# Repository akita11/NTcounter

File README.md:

# NTcounter

赤外線の送信機・受信機のペアで、その間を横切った数をカウントするシステムです。NT金沢のような開放空間での来場者カウントに使います。横切りがあった時刻と積算カウント数をmicroSDカードに記録していきます。

# 用意するもの
## 送信機
- [ATtiny10](http://akizukidenshi.com/catalog/g/gI-04575/)
- [nMOS](http://akizukidenshi.com/catalog/g/gI-06051/)
- [赤外線LED](http://akizukidenshi.com/catalog/g/gI-12612/)
- USB Type-Cコネクタ (a)http://www.aitendo.com/product/17279 または (b)http://akizukidenshi.com/catalog/g/gC-14356/
- チップ抵抗 5.1kΩ(1608)×2個、1kΩ(1608)×1個
- チップLED 緑(1608)×1個
- プリント基板 NTcounterTX
- [100均ルーペNo.13058]（セリア等で売っているようです）

- 厚紙
- MDF板(厚さ6mm) ※アクリル板(厚さ5mm)でもOK
- USBモバイルバッテリ等の電源と、それをつなぐUSB Type-C等のケーブル
- M3x12ネジ+M3ナット×2組

## 受信機
- [M5Stack Basic](https://www.switch-science.com/catalog/3647/)
- [M5Stackバッテリモジュール](https://www.switch-science.com/catalog/3653/)
- [M5Stackコネクタ](https://www.switch-science.com/catalog/3654/)
- [赤外線リモコン受信機](http://akizukidenshi.com/catalog/g/gI-04659/)
- [スライドスイッチ](http://akizukidenshi.com/catalog/g/gP-08789/)
- [ピンソケット1x3p](http://akizukidenshi.com/catalog/g/gC-10098/)
- プリント基板 NTcounterRX
- microSDカード
- アクリル板(厚さ5mm)

※おまけ：プリント基板NTcounerRXは、M5StackのGroveコネクタのポートA, B, C, D, Eの拡張にも使えます

# 作り方

## 送信機

1. プリント基板NTcounterTXに部品をとりつけます。USB Type-Cコネクタとして(a)を用いる場合はCN4に、(b)を使う場合はCN2にとりつけます。なおCN4につける(a)の方がはんだ付けはしやすいです。
2. 、ファームウエアNTcounterTX.hexを書き込みます。(NTcounterTX.inoをArduinoIDEからコンパイルして書き込んでもOK。（参考: [ArduinoIDEでATtiny10を開発・書き込み ](https://make.kosakalab.com/make/electronic-work/arduino-ide/arduino_tpi/)
3. MDF板(厚さ6mm)にNTcounerTX_lens.svgの右側の部品をレーザーカッター等でカットし、1.を固定します。

4. 厚紙にNTcounerTX_lens.svgの左側の部品をレーザーカッター等でカットします。このとき、用いるUSB-Cコネクタが(a)の場合と(b)の場合で少し加工データが異なるので、NTcounerTX_lens.svgを適宜修正してください。

5. 100均ルーペの3倍を、取っ手を外して、1.とともに、2.で囲って固定します。

## 受信機

1. プリント基板NTcounterRXに部品をとりつけます。（※M5Stackコネクタのオス・メスを取り付ける面を間違えないように注意。M5Stack本体(M5Core)に差し込んだ状態でシルク文字が外から見える向き）
2. VSCodeでNTcounerRX内のファームウエアの以下の箇所を自分の環境に合わせて修正します。
  - #define DEV_NAME "NTcounter" ← デバイス名。ログファイルの冒頭に記録される
  - const char* ssid       = "****"; ← 起動時に接続するWiFiアクセスポイントのSSID
  - const char* password   = "****"; ← 同パスワード
3. ファームウエアをビルドして書き込みます。
4. アクリル板(厚さ5mm)をNTcounterRX_spaccer.svgのようにレーザーカッター等でカットします。
5. M5StackのCore、1.とスペーサ、M5Stackバッテリユニット、、M5Stack底板を順にとりつけます。

# 使い方
1. USBモバイルバッテリ等からUSB TypeｰCケーブルで送信機に給電します。電源ランプが点灯します。
2. 受信機を充電後、microSDカードをとりつけて電源スイッチをONにします。なお受信機の起動時のみ、時刻あわせのためWiFi接続が必要です。起動後はWiFiは不要です。
3. 送信機と受信機を向かい合わせに、通路をはさむ両側に置ます。このとき、送信機の赤外光が受信機に届いていれば、受信機のディスプレイに表示される円が緑になります。円が赤い場合は、赤外光が届いていないので、向きを調整します。両者の間隔は1〜6mくらいまでは大丈夫なはずです。
4. この状態で、両者の間に障害物を置くと、受信機に表示される円が赤になり、その時点の時刻と積算カウント数が記録されます。
5. 動作がOKそうなら、受信機のM5StackのBボタン（中央ボタン）を押し、画面表示をOFFにすると、バッテリが長持ちします。（満充電で丸2日くらいはもつはず）

# Author

@akita11 (akita@ifdl.jp)

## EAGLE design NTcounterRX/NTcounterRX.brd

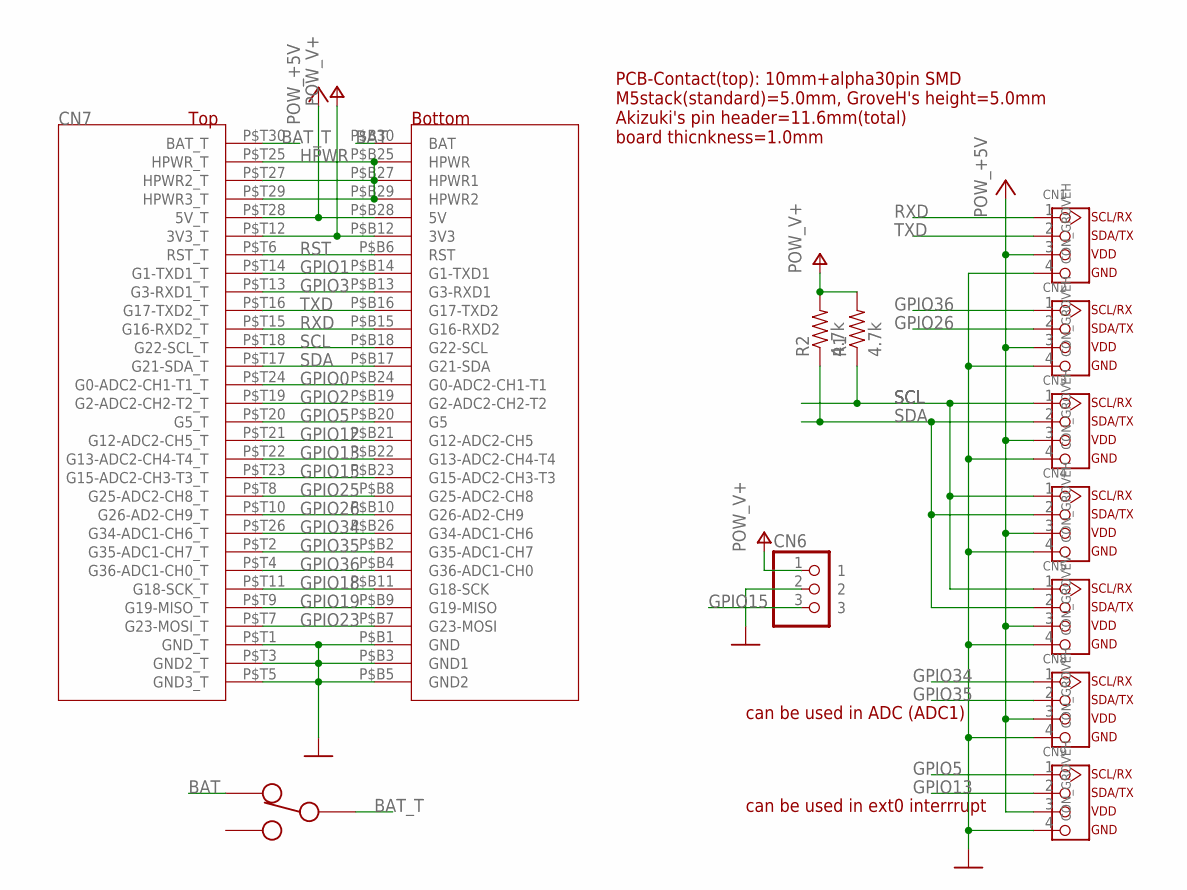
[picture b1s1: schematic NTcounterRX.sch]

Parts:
CN1, CN2, CN3, CN4, CN8, CN9: CON_GROVEH; CON_GROVE_H
CN5: CON_GROVEV; CON_GROVE_V
CN6: CON_PINHD-1X3R; 1X03R
CN7: MBUS_SEPBAT; MBUS_SEP_BAT_SHORT
R1, R2: 4.7k; 0603
SW1: SW_SLIDESK12D01; SW_SK12D01

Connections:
+5V: CN1.3, CN2.3, CN3.3, CN4.3, CN5.3, CN7.P$B28 (5V), CN7.P$T28 (5V_T), CN8.3, CN9.3
BAT: CN7.P$B30 (BAT), SW1.P$1
BAT_T: CN7.P$T30 (BAT_T), SW1.P$2
GND: CN1.4, CN2.4, CN3.4, CN4.4, CN5.4, CN6.2, CN7.P$B1 (GND), CN7.P$B3 (GND1), CN7.P$B5 (GND2), CN7.P$T1 (GND_T), CN7.P$T3 (GND2_T), CN7.P$T5 (GND3_T), CN8.4, CN9.4
GPIO0: CN7.P$B24 (G0-ADC2-CH1-T1), CN7.P$T24 (G0-ADC2-CH1-T1_T)
GPIO1: CN7.P$B14 (G1-TXD1), CN7.P$T14 (G1-TXD1_T)
GPIO2: CN7.P$B19 (G2-ADC2-CH2-T2), CN7.P$T19 (G2-ADC2-CH2-T2_T)
GPIO3: CN7.P$B13 (G3-RXD1), CN7.P$T13 (G3-RXD1_T)
GPIO5: CN7.P$B20 (G5), CN7.P$T20 (G5_T), CN9.1
GPIO12: CN7.P$B21 (G12-ADC2-CH5), CN7.P$T21 (G12-ADC2-CH5_T)
GPIO13: CN7.P$B22 (G13-ADC2-CH4-T4), CN7.P$T22 (G13-ADC2-CH4-T4_T), CN9.2
GPIO15: CN6.3, CN7.P$B23 (G15-ADC2-CH3-T3), CN7.P$T23 (G15-ADC2-CH3-T3_T)
GPIO18: CN7.P$B11 (G18-SCK), CN7.P$T11 (G18-SCK_T)
GPIO19: CN7.P$B9 (G19-MISO), CN7.P$T9 (G19-MISO_T)
GPIO23: CN7.P$B7 (G23-MOSI), CN7.P$T7 (G23-MOSI_T)
GPIO25: CN7.P$B8 (G25-ADC2-CH8), CN7.P$T8 (G25-ADC2-CH8_T)
GPIO26: CN2.2, CN7.P$B10 (G26-AD2-CH9), CN7.P$T10 (G26-AD2-CH9_T)
GPIO34: CN7.P$B26 (G34-ADC1-CH6), CN7.P$T26 (G34-ADC1-CH6_T), CN8.1
GPIO35: CN7.P$B2 (G35-ADC1-CH7), CN7.P$T2 (G35-ADC1-CH7_T), CN8.2
GPIO36: CN2.1, CN7.P$B4 (G36-ADC1-CH0), CN7.P$T4 (G36-ADC1-CH0_T)
HPWR: CN7.P$B25 (HPWR), CN7.P$B27 (HPWR1), CN7.P$B29 (HPWR2), CN7.P$T25 (HPWR_T), CN7.P$T27 (HPWR2_T), CN7.P$T29 (HPWR3_T)
P$3: SW1.P$3
RST: CN7.P$B6 (RST), CN7.P$T6 (RST_T)
RXD: CN1.1, CN7.P$B15 (G16-RXD2), CN7.P$T15 (G16-RXD2_T)
SCL: CN3.1, CN4.1, CN5.1, CN7.P$B18 (G22-SCL), CN7.P$T18 (G22-SCL_T), R1.1
SDA: CN3.2, CN4.2, CN5.2, CN7.P$B17 (G21-SDA), CN7.P$T17 (G21-SDA_T), R2.1
TXD: CN1.2, CN7.P$B16 (G17-TXD2), CN7.P$T16 (G17-TXD2_T)
V+: CN6.1, CN7.P$B12 (3V3), CN7.P$T12 (3V3_T), R1.2, R2.2

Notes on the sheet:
PCB-Contact(top): 10mm+alpha30pin SMD M5stack(standard)=5.0mm, GroveH's height=5.0mm Akizuki's pin header=11.6mm(total) board thicnkness=1.0mm
can be used in ext0 interrrupt
can be used in ADC (ADC1)

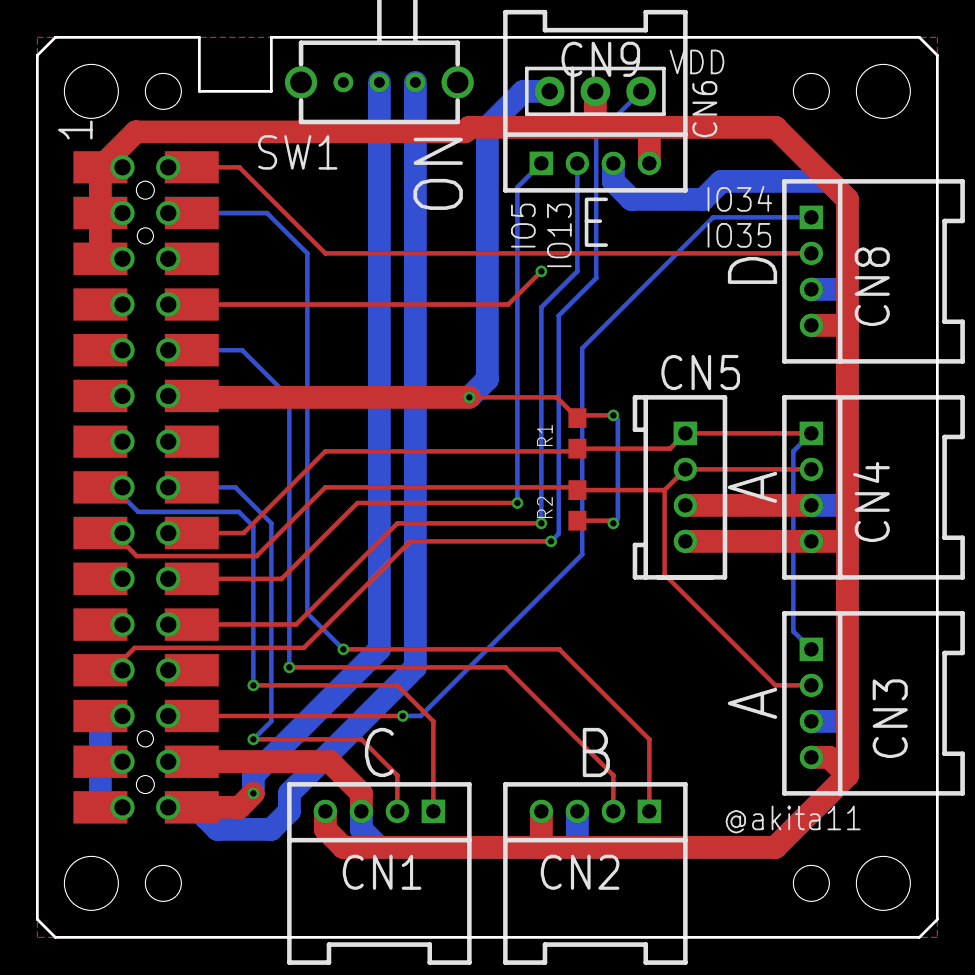
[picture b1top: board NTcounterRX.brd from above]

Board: 2 copper layers, 50.0 x 50.0 mm, 12 parts (0 on the bottom side), 27 nets.

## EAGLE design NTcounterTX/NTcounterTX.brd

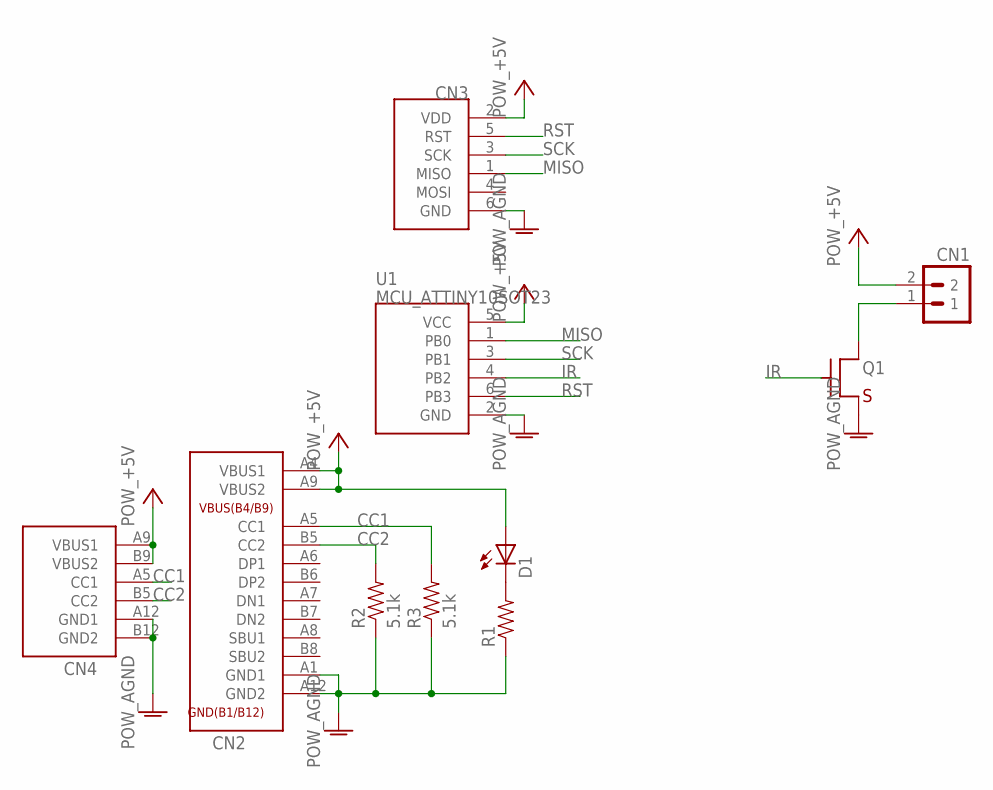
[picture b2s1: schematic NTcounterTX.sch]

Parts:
CN1: CON_PINHD-1X2LOCK; SPARKFUN_1X02_LOCK
CN2: CON_USB-C-16TH; USB-C_16P_TH
CN3: CON_AVRISPTH; 2X03R
CN4: CON_USB-C-6; USB-C_6P
D1: LED0603; SPARKFUN_LED-0603
Q1: TR_NMOS_IRLML6344; SOT-23-3-2916
R1: RES0603; 0603
R2, R3: 5.1k; 0603
U1: MCU_ATTINY10SOT23; SOT23-6

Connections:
+5V: CN1.2, CN2.A4 (VBUS1), CN2.A9 (VBUS2), CN3.2 (VDD), CN4.A9 (VBUS1), CN4.B9 (VBUS2), D1.A, U1.5 (VCC)
AGND: CN2.A1 (GND1), CN2.A12 (GND2), CN3.6 (GND), CN4.A12 (GND1), CN4.B12 (GND2), Q1.2 (S), R1.1, R2.1, R3.1, U1.2 (GND)
CC1: CN2.A5 (CC1), CN4.A5 (CC1), R3.2
CC2: CN2.B5 (CC2), CN4.B5 (CC2), R2.2
IR: Q1.1 (G), U1.4 (PB2)
MISO: CN3.1 (MISO), U1.1 (PB0)
unnamed: CN1.1, Q1.3 (D)
unnamed: D1.C, R1.2
RST: CN3.5 (RST), U1.6 (PB3)
SCK: CN3.3 (SCK), U1.3 (PB1)

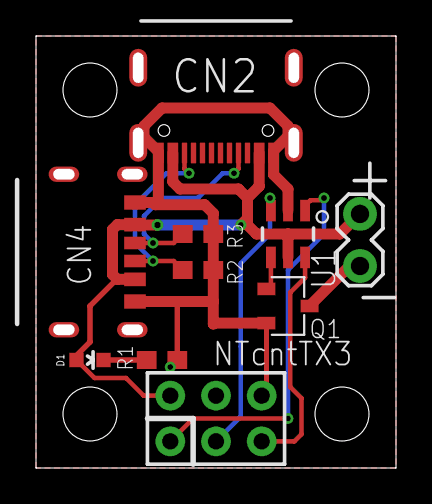
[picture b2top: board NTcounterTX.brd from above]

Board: 2 copper layers, 20.0 x 24.0 mm, 10 parts (0 on the bottom side), 10 nets.

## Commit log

2020-03-03 一通りのデータを配置
2020-03-03 README.mdの誤字を修正
2020-03-03 送信機の基板固定板のデータを微調整
2020-03-06 送信機のUSB-Cコネクタについて追記・修正
2020-03-09 送信機のルーペに関する記述を追加
2020-03-09 ルーペの写真を追加
